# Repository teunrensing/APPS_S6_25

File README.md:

# APPS_S6_25
Dit is een repo voor het APPS project

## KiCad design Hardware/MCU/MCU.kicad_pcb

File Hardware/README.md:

# APPS_S6_25 Hardware
APPS Hardware

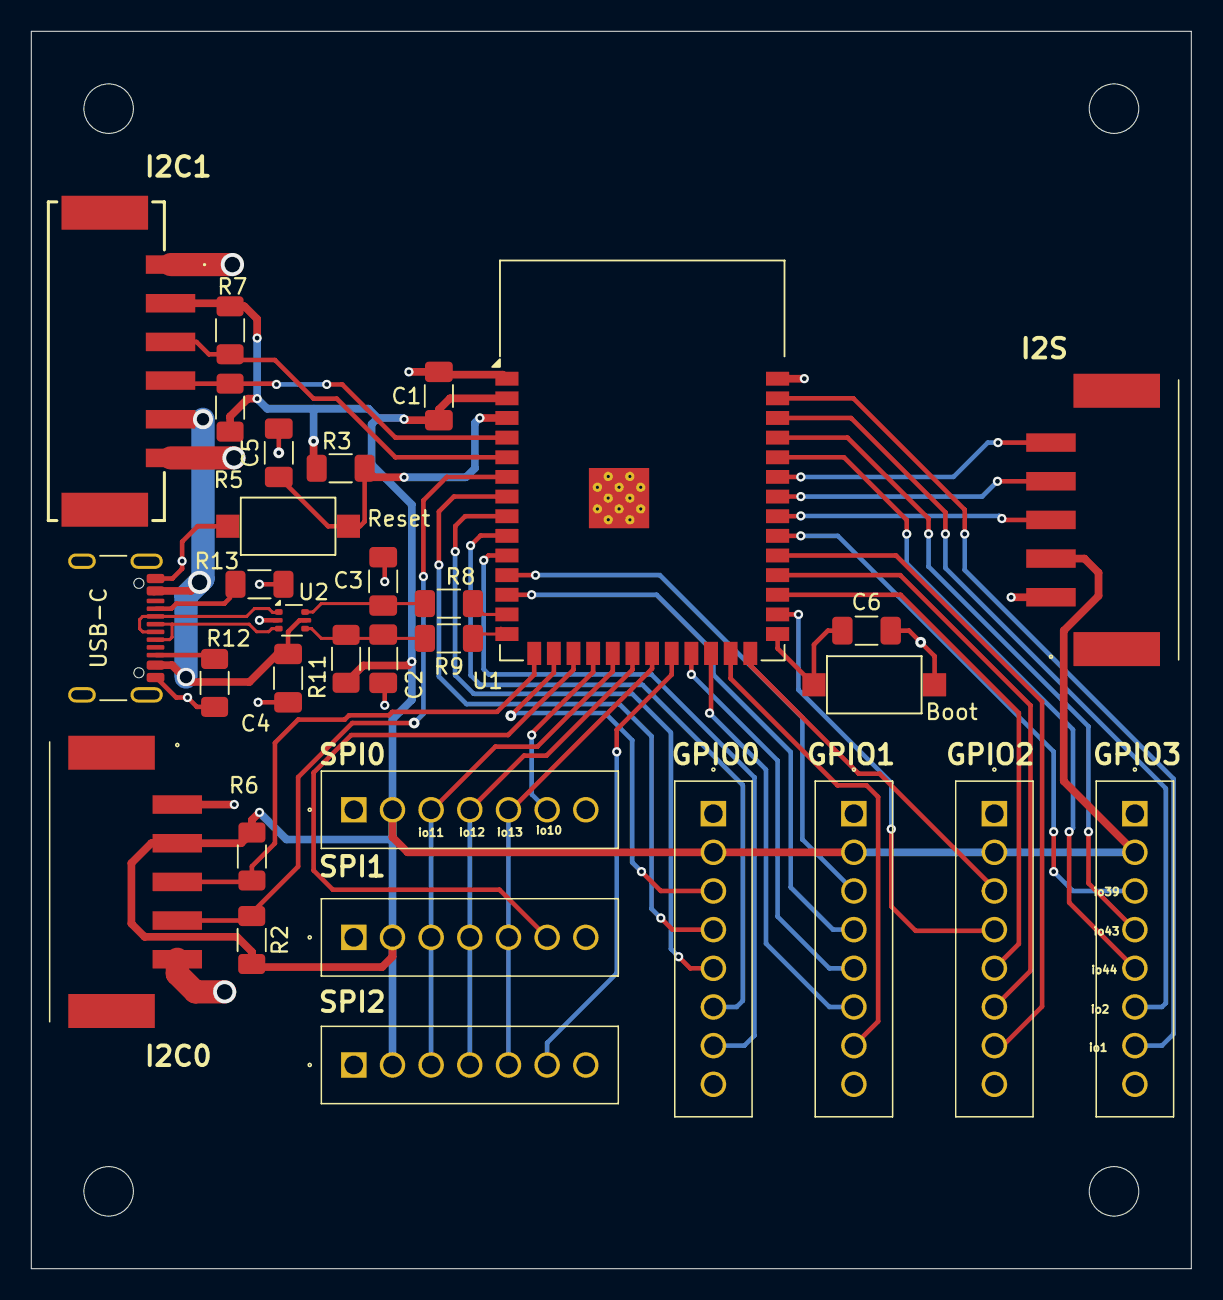
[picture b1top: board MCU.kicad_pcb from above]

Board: 4 copper layers, 75.0 x 80.0 mm, 35 parts (0 on the bottom side), 47 nets.

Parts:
Boot: SW_Push; SW_SPST_CK_RS282G05A3
C1: 100n; C_1206_3216Metric_Pad1.33x1.80mm_HandSolder
C2, C3: C; C_1206_3216Metric_Pad1.33x1.80mm_HandSolder
C4: 100nf; C_1206_3216Metric_Pad1.33x1.80mm_HandSolder
C5, C6: 1u; C_1206_3216Metric_Pad1.33x1.80mm_HandSolder
GPIO0, GPIO1, GPIO2, GPIO3: 1778612
H1, H2, H3, H4: MountingHole; MountingHole_3.2mm_M3
I2C0: i2c1; 1814948
I2C1: i2c0; 1814951
I2S: i2s; 1814948
R2, R5, R6, R7: 4k7; R_1206_3216Metric_Pad1.30x1.75mm_HandSolder
R3: 10k; R_1206_3216Metric_Pad1.30x1.75mm_HandSolder
R8, R9: 0; R_1206_3216Metric_Pad1.30x1.75mm_HandSolder
R11, R12, R13: 5k1; R_1206_3216Metric_Pad1.30x1.75mm_HandSolder
Reset: SW_Push; SW_SPST_CK_RS282G05A3
SPI0: spi0; 1778609
SPI1: sp1; 1778609
SPI2: sp2; 1778609
U1: ESP32-S3-WROOM-1
U2: USBLC6-2P6; SOT-666
USB-C: USB_C_Receptacle_USB2.0_16P; USB_C_Receptacle_GCT_USB4105-xx-A_16P_TopMnt_Horizontal

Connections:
+: C2.2, R9.2, R11.2, U2.4 (I/O2)
+3.3V: C1.2, GPIO0.2, GPIO1.2, GPIO2.2, GPIO3.2, I2C0.2, I2C1.2, I2S.2, R2.2, R3.1, R5.2, R6.1, R7.1, R11.1, SPI0.2, SPI1.2, SPI2.2, U1.2 (3V3)
+5Vin: GPIO0.8, GPIO1.8, GPIO2.8, GPIO3.8, I2C0.5, I2C1.6, SPI0.7, SPI1.7, SPI2.7
+5Vout: C4.1, I2C1.5, U2.5 (VBUS), USB-C.A4 (VBUS), USB-C.A9 (VBUS), USB-C.B4 (VBUS), USB-C.B9 (VBUS)
-: C3.2, R8.2, U2.6 (I/O1)
GND: Boot.2, C1.1, C2.1, C3.1, C4.2, C5.2, C6.2, GPIO0.1, GPIO1.1, GPIO2.1, GPIO3.1, I2C0.1, I2C1.1, I2S.1, R12.1, R13.1, Reset.2, SPI0.1, SPI1.1, SPI2.1, U1.1 (GND), U1.40 (GND), U1.41 (GND), U2.2 (GND), USB-C.A1 (GND), USB-C.A12 (GND), USB-C.B1 (GND), USB-C.B12 (GND), USB-C.S1 (SHIELD)
unnamed: R13.2, USB-C.A5 (CC1)
unnamed: R12.2, USB-C.B5 (CC2)
unnamed: U2.3 (I/O2), USB-C.A6 (D+), USB-C.B6 (D+)
unnamed: U2.1 (I/O1), USB-C.A7 (D-), USB-C.B7 (D-)
unnamed: R9.1, U1.14 (USB_D+)
unnamed: R8.1, U1.13 (USB_D-)
boot0: Boot.1, C6.1, U1.27 (IO0)
i2s sck: I2S.3, U1.33 (IO40)
i2s sd: I2S.5, U1.35 (IO42)
i2s ws: I2S.4, U1.34 (IO41)
io1: GPIO3.7, U1.39 (IO1)
io2: GPIO3.6, U1.38 (IO2)
io7: GPIO0.4, U1.7 (IO7)
io8: GPIO1.4, U1.12 (IO8)
io15: GPIO0.5, U1.8 (IO15)
io16: GPIO0.6, U1.9 (IO16)
io17: GPIO0.7, U1.10 (IO17)
io18: GPIO1.3, U1.11 (IO18)
io21: GPIO1.5, U1.23 (IO21)
io35: GPIO2.4, U1.28 (IO35)
io36: GPIO2.5, U1.29 (IO36)
io37: GPIO2.6, U1.30 (IO37)
io38: GPIO2.7, U1.31 (IO38)
io39: GPIO3.3, U1.32 (IO39)
io45: GPIO2.3, U1.26 (IO45)
io46: GPIO0.3, U1.16 (IO46)
io47: GPIO1.6, U1.24 (IO47)
io48: GPIO1.7, U1.25 (IO48)
miso: SPI0.5, SPI1.5, SPI2.5, U1.21 (IO13)
mosi: SPI0.3, SPI1.3, SPI2.3, U1.19 (IO11)
reset: C5.1, R3.2, Reset.1, U1.3 (EN)
rxd0: GPIO3.5, U1.36 (RXD0)
sck: SPI0.4, SPI1.4, SPI2.4, U1.20 (IO12)
scl0: I2C0.4, R2.1, U1.6 (IO6)
scl1: I2C1.4, R5.1, U1.4 (IO4)
sda0: I2C0.3, R6.2, U1.15 (IO3)
sda1: I2C1.3, R7.2, U1.5 (IO5)
ss0: SPI0.6, U1.18 (IO10)
ss1: SPI1.6, U1.17 (IO9)
ss2: SPI2.6, U1.22 (IO14)
txd0: GPIO3.4, U1.37 (TXD0)

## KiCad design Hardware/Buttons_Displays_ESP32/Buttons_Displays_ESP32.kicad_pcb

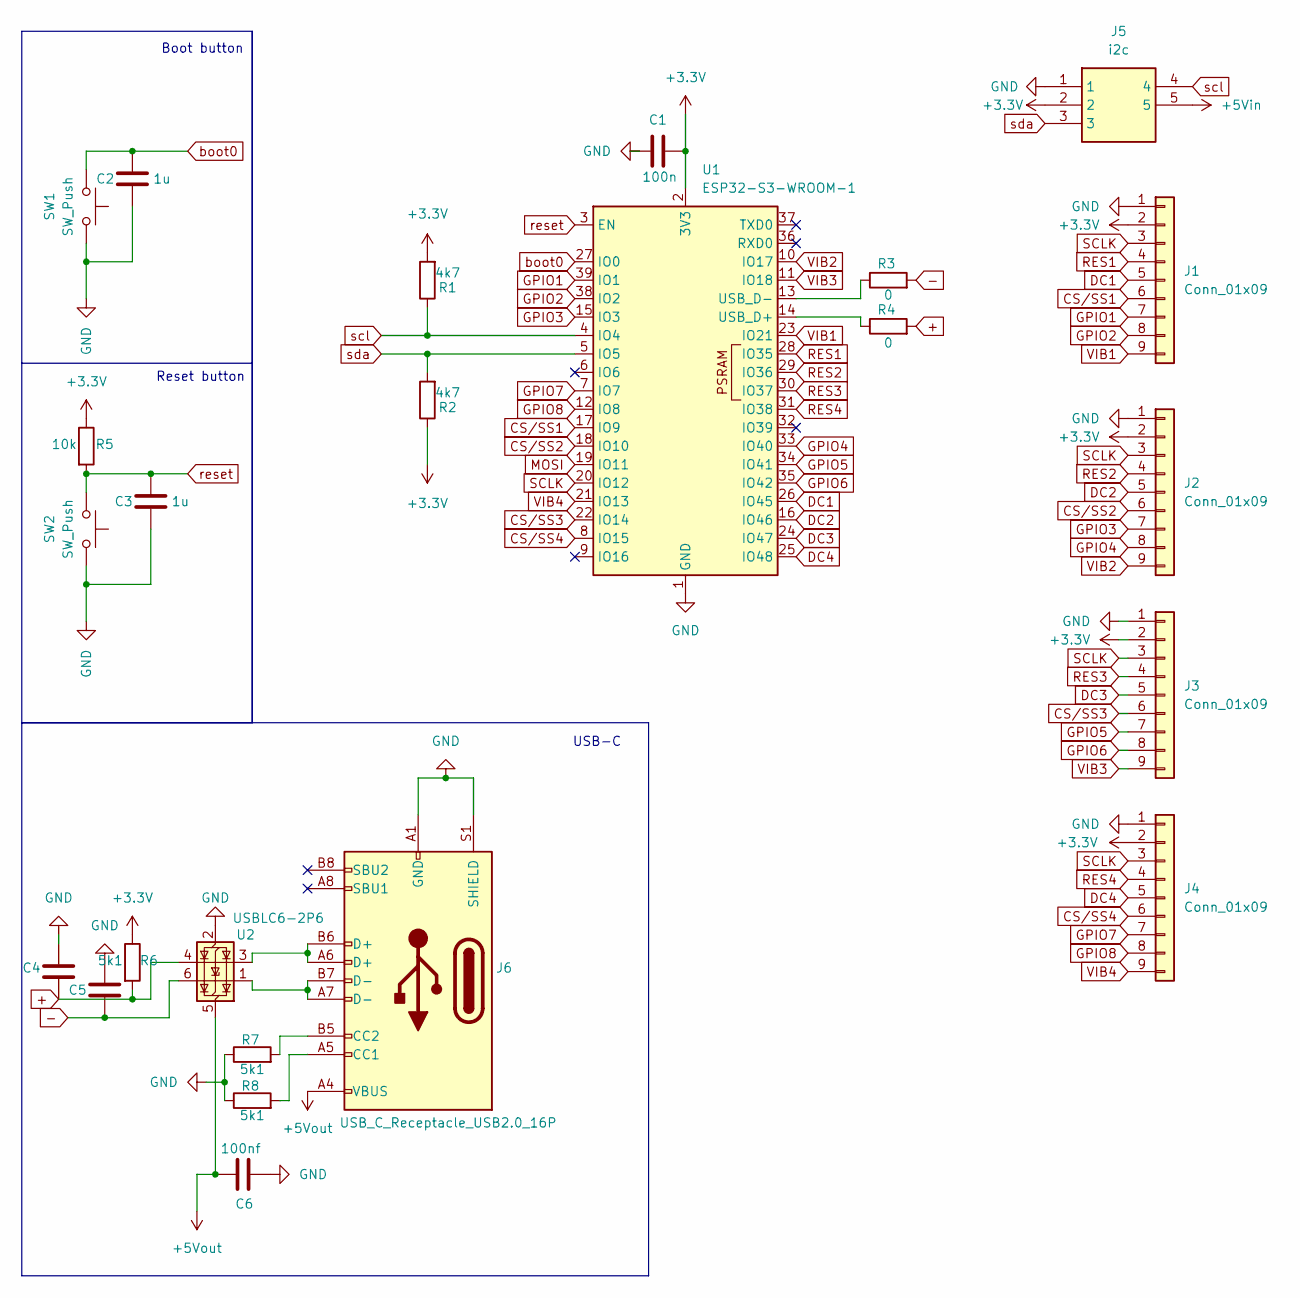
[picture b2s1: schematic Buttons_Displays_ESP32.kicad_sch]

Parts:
C1: 100n; C_1206_3216Metric_Pad1.33x1.80mm_HandSolder
C2, C3: 1u; C_1206_3216Metric_Pad1.33x1.80mm_HandSolder
C4, C5: C; C_1206_3216Metric_Pad1.33x1.80mm_HandSolder
C6: 100nf; C_1206_3216Metric_Pad1.33x1.80mm_HandSolder
J1, J2, J3, J4: Conn_01x09; JST_XH_B9B-XH-A_1x09_P2.50mm_Vertical
J5: i2c; 1814948; Mouser Part Number 651-1814948
J6: USB_C_Receptacle_USB2.0_16P; USB_C_Receptacle_GCT_USB4105-xx-A_16P_TopMnt_Horizontal
R1, R2: 4k7; R_1206_3216Metric_Pad1.30x1.75mm_HandSolder
R3, R4: 0; R_1206_3216Metric_Pad1.30x1.75mm_HandSolder
R5: 10k; R_1206_3216Metric_Pad1.30x1.75mm_HandSolder
R6, R7, R8: 5k1; R_1206_3216Metric_Pad1.30x1.75mm_HandSolder
SW1, SW2: SW_Push; SW_SPST_CK_RS282G05A3
U1: ESP32-S3-WROOM-1
U2: USBLC6-2P6; SOT-666

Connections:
+: C4.2, R4.2, R6.2, U2.4 (I/O2)
+3.3V: C1.2, J1.2, J2.2, J3.2, J4.2, J5.2, R1.2, R2.1, R5.1, R6.1, U1.2 (3V3)
+5Vin: J5.5
+5Vout: C6.1, J6.A4 (VBUS), J6.A9 (VBUS), J6.B4 (VBUS), J6.B9 (VBUS), U2.5 (VBUS)
-: C5.2, R3.2, U2.6 (I/O1)
CS/SS1: J1.6, U1.17 (IO9)
CS/SS2: J2.6, U1.18 (IO10)
CS/SS3: J3.6, U1.22 (IO14)
CS/SS4: J4.6, U1.8 (IO15)
DC1: J1.5, U1.26 (IO45)
DC2: J2.5, U1.16 (IO46)
DC3: J3.5, U1.24 (IO47)
DC4: J4.5, U1.25 (IO48)
GND: C1.1, C2.2, C3.2, C4.1, C5.1, C6.2, J1.1, J2.1, J3.1, J4.1, J5.1, J6.A1 (GND), J6.A12 (GND), J6.B1 (GND), J6.B12 (GND), J6.S1 (SHIELD), R7.1, R8.1, SW1.2, SW2.2, U1.1 (GND), U1.40 (GND), U1.41 (GND), U2.2 (GND)
GPIO1: J1.7, U1.39 (IO1)
GPIO2: J1.8, U1.38 (IO2)
GPIO3: J2.7, U1.15 (IO3)
GPIO4: J2.8, U1.33 (IO40)
GPIO5: J3.7, U1.34 (IO41)
GPIO6: J3.8, U1.35 (IO42)
GPIO7: J4.7, U1.7 (IO7)
GPIO8: J4.8, U1.12 (IO8)
MOSI: U1.19 (IO11)
unnamed: J6.A5 (CC1), R8.2
unnamed: J6.B5 (CC2), R7.2
unnamed: J6.A6 (D+), J6.B6 (D+), U2.3 (I/O2)
unnamed: J6.A7 (D-), J6.B7 (D-), U2.1 (I/O1)
unnamed: R4.1, U1.14 (USB_D+)
unnamed: R3.1, U1.13 (USB_D-)
RES1: J1.4, U1.28 (IO35)
RES2: J2.4, U1.29 (IO36)
RES3: J3.4, U1.30 (IO37)
RES4: J4.4, U1.31 (IO38)
SCLK: J1.3, J2.3, J3.3, J4.3, U1.20 (IO12)
VIB1: J1.9, U1.23 (IO21)
VIB2: J2.9, U1.10 (IO17)
VIB3: J3.9, U1.11 (IO18)
VIB4: J4.9, U1.21 (IO13)
boot0: C2.1, SW1.1, U1.27 (IO0)
reset: C3.1, R5.2, SW2.1, U1.3 (EN)
scl: J5.4, R1.1, U1.4 (IO4)
sda: J5.3, R2.2, U1.5 (IO5)

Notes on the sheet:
Boot button
USB-C
Reset button

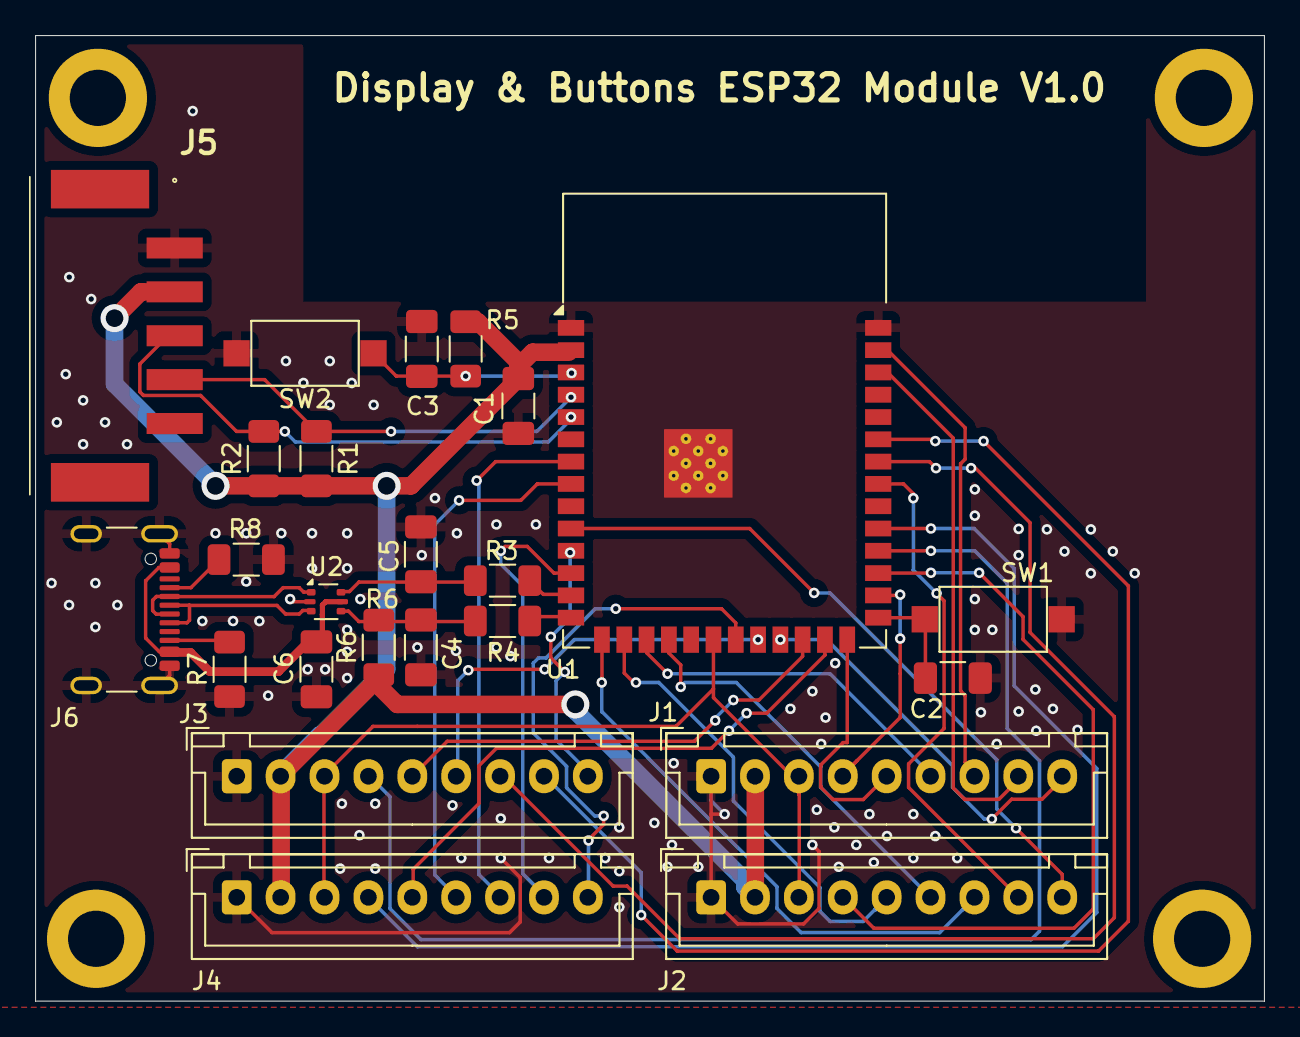
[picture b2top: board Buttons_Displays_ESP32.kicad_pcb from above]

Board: 2 copper layers, 70.0 x 55.0 mm, 24 parts (0 on the bottom side), 40 nets.

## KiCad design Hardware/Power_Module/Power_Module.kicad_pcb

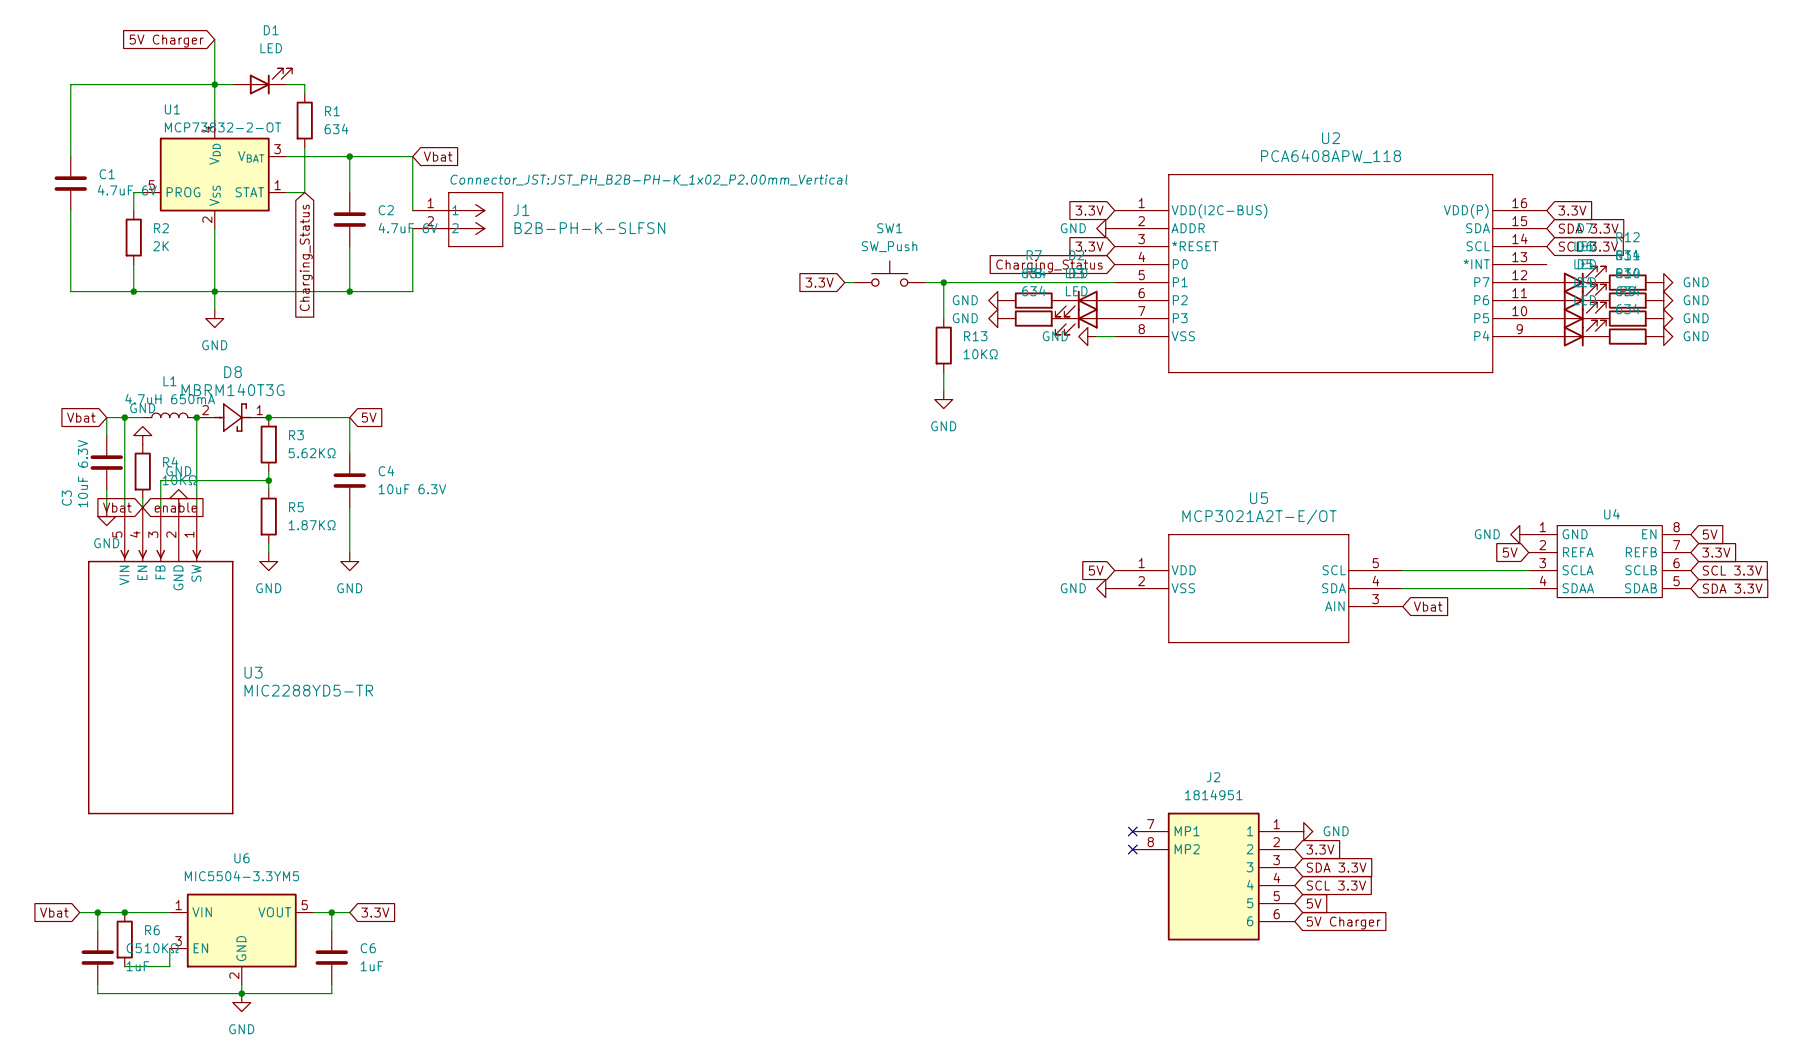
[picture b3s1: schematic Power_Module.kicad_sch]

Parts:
C1, C2: 4.7uF 6V; C_1206_3216Metric
C3, C4: 10uF 6.3V; C_0805_2012Metric
C5, C6: 1uF; C_0402_1005Metric
D1, D2, D3, D4, D5, D6, D7: LED; LED_0402_1005Metric
D8: MBRM140T3G; D_SOD-123
J1: B2B-PH-K-SLFSN; JST_PH_B2B-PH-K_1x02_P2.00mm_Vertical
J2: 1814951; Manufacturer_Part_Number 1814951; Mouser Part Number 651-1814951
L1: 4.7uH 650mA; C_1210_3225Metric
R1, R7, R8, R9, R10, R11, R12: 634; C_0402_1005Metric
R2: 2K; R_0402_1005Metric
R3: 5.62KΩ; R_0603_1608Metric
R4, R6, R13: 10KΩ; R_0603_1608Metric
R5: 1.87KΩ; R_0603_1608Metric
SW1: SW_Push; SW_Tactile_SPST_NO_Straight_CK_PTS636Sx25SMTRLFS
U1: MCP73832-2-OT; SOT-23-5
U2: PCA6408APW_118; TSSOP-16_4.4x5mm_P0.65mm
U3: MIC2288YD5-TR; TSOT-23-5
U4: TSSOP-8_3x3mm_P0.65mm
U5: MCP3021A2T-E/OT; TSOT-23-5
U6: MIC5504-3.3YM5; SOT-23-5

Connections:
3.3V: C6.1, J2.2, SW1.1, U2.1 (VDD(I2C-BUS)), U2.3 (*RESET), U2.16 (VDD(P)), U4.7 (REFB), U6.5 (VOUT)
5V: C4.1, D8.1, J2.5, R3.2, U4.2 (REFA), U4.8 (EN), U5.1 (VDD)
5V Charger: C1.1, D1.2 (A), J2.6, U1.4 (V_{DD})
Charging_Status: R1.2, U1.1 (STAT), U2.4 (P0)
GND: C1.2, C2.2, C3.2, C4.2, C5.2, C6.2, J1.2, J2.1, R2.2, R4.1, R5.2, R7.1, R8.1, R9.2, R10.2, R11.2, R12.2, R13.2, U1.2 (V_{SS}), U2.2 (ADDR), U2.8 (VSS), U3.2 (GND), U4.1 (GND), U5.2 (VSS), U6.2 (GND)
unnamed: D1.1 (K), R1.1
unnamed: D2.2 (A), U2.6 (P2)
unnamed: D2.1 (K), R7.2
unnamed: D3.2 (A), U2.7 (P3)
unnamed: D3.1 (K), R8.2
unnamed: D4.2 (A), U2.9 (P4)
unnamed: D4.1 (K), R9.1
unnamed: D5.2 (A), U2.10 (P5)
unnamed: D5.1 (K), R10.1
unnamed: D6.2 (A), U2.11 (P6)
unnamed: D6.1 (K), R11.1
unnamed: D7.2 (A), U2.12 (P7)
unnamed: D7.1 (K), R12.1
unnamed: R2.1, U1.5 (PROG)
unnamed: R13.1, SW1.2, U2.5 (P1)
unnamed: R3.1, R5.1, U3.3 (FB)
unnamed: D8.2, L1.2, U3.1 (SW)
unnamed: U4.3 (SCLA), U5.5 (SCL)
unnamed: U4.4 (SDAA), U5.4 (SDA)
unnamed: R6.2, U6.3 (EN)
SCL 3.3V: J2.4, U2.14 (SCL), U4.6 (SCLB)
SDA 3.3V: J2.3, U2.15 (SDA), U4.5 (SDAB)
Vbat: C2.1, C3.1, C5.1, J1.1, L1.1, R4.2, R6.1, U1.3 (V_{BAT}), U3.4 (EN), U3.5 (VIN), U5.3 (AIN), U6.1 (VIN)

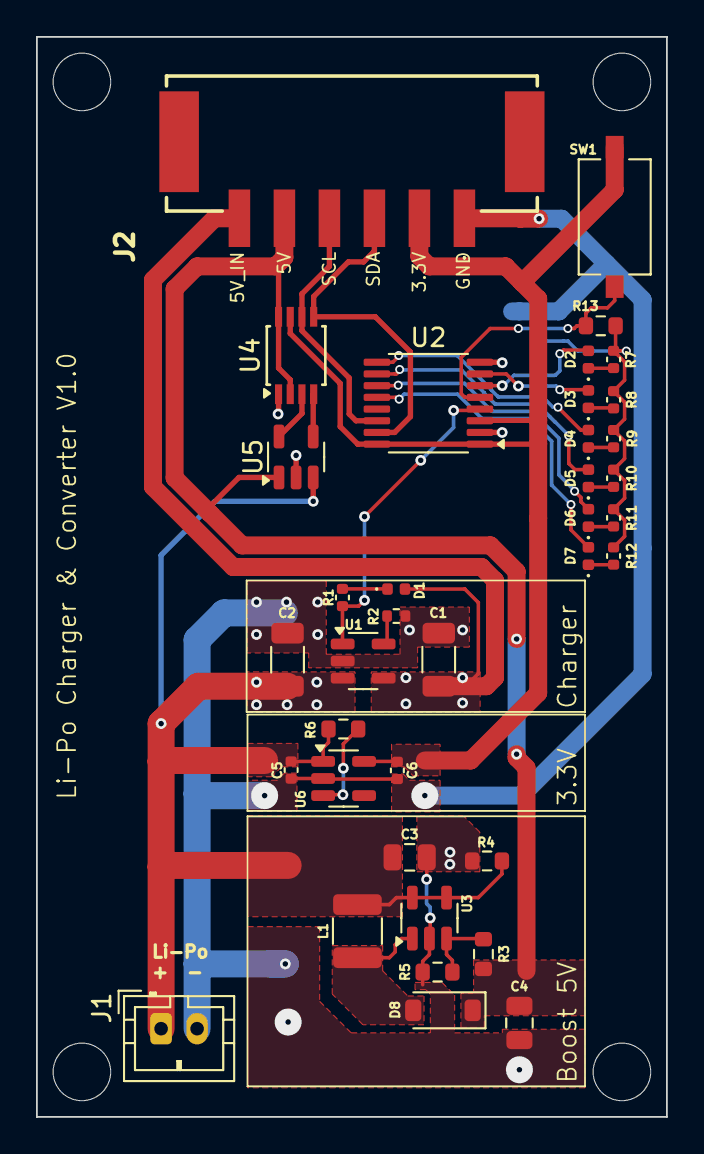
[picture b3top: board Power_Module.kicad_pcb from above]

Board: 2 copper layers, 35.0 x 60.0 mm, 37 parts (0 on the bottom side), 28 nets.

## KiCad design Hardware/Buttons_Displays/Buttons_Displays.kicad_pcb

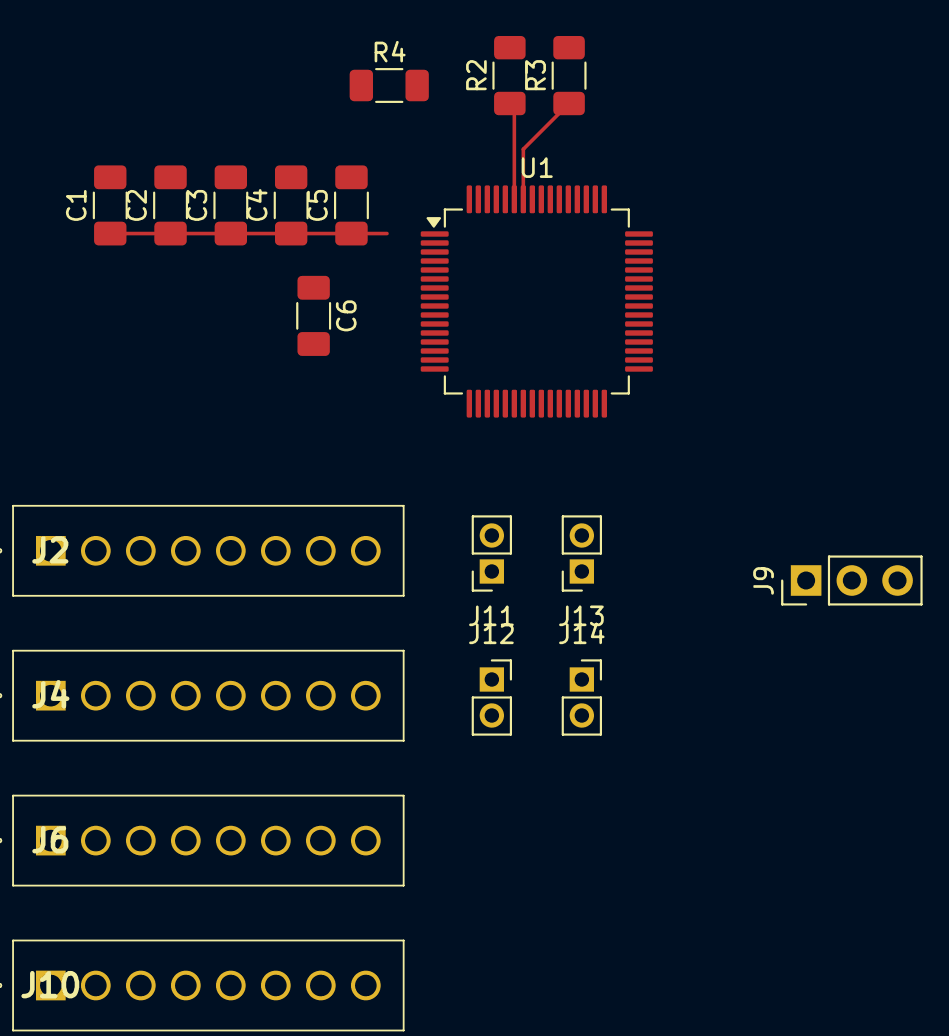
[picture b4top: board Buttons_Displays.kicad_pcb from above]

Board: 2 copper layers, 19 parts (0 on the bottom side), 26 nets.

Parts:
C1: 10u; C_1206_3216Metric_Pad1.33x1.80mm_HandSolder
C2, C3, C4, C5, C6: 100n; C_1206_3216Metric_Pad1.33x1.80mm_HandSolder
J2, J4, J6, J10: Conn_01x08; 1778612
J9: Conn_01x03; PinHeader_1x03_P2.54mm_Vertical
J11, J12, J13, J14: Conn_01x02; PinSocket_1x02_P2.00mm_Vertical
R2, R3: 4k7; R_1206_3216Metric_Pad1.30x1.75mm_HandSolder
R4: 10k; R_1206_3216Metric_Pad1.30x1.75mm_HandSolder
U1: STM32H523RETx; LQFP-64_10x10mm_P0.5mm

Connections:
+3.3V: C1.1, C2.1, C3.1, C4.1, C5.1, J2.7, J4.7, J6.7, J10.7, R2.2, R3.2, U1.1 (VBAT), U1.19 (VDD), U1.32 (VDD), U1.48 (VDD), U1.64 (VDD)
CS/SS: J2.2, J4.2, J6.2, J10.2, U1.20 (PA4)
DC1: J10.3, U1.8 (PC0)
DC2: J2.3, U1.9 (PC1)
DC3: J4.3, U1.10 (PC2)
DC4: J6.3, U1.11 (PC3)
GND: C1.2, C2.2, C3.2, C4.2, C5.2, C6.2, J2.1, J4.1, J6.1, J10.1, J11.1, J12.1, J13.1, J14.1, U1.12 (VSSA), U1.18 (VSS), U1.31 (VSS), U1.47 (VSS), U1.63 (VSS)
GPIO1: J10.8, U1.26 (PB0)
GPIO2: J11.2, U1.27 (PB1)
GPIO3: J2.8, U1.28 (PB2)
GPIO4: J12.2, U1.57 (PB5)
GPIO5: J4.8, U1.61 (PB8)
GPIO6: J13.2, U1.29 (PB10)
GPIO7: J6.8, U1.33 (PB12)
GPIO8: J14.2, U1.34 (PB13)
NRST: C6.1, J9.3, U1.7 (NRST)
unnamed: R4.2, U1.60 (BOOT0)
RES1: J10.4, U1.41 (PA8)
RES2: J2.4, U1.42 (PA9)
RES3: J4.4, U1.43 (PA10)
RES4: J6.4, U1.44 (PA11)
SCLK: J2.6, J4.6, J6.6, J10.6, U1.21 (PA5)
SWCLK: J9.1, U1.49 (PA14(JTCK)
SWDIO: J9.2, U1.46 (PA13(JTMS)
scl: R2.1, U1.59 (PB7)
sda: R3.1, U1.58 (PB6)

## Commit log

2025-02-06 Folders toegevoegd
2025-02-06 Ignore naar de software folder
2025-02-06 kicad gitignore
2025-02-13 kicad project
2025-02-19 inmp + mp3player
2025-02-19 added MCU
2025-03-12 Added power module project
2025-03-12 buttondisplay
2025-03-12 added gnd for test
2025-03-13 MCU schema bijgewerkt
2025-03-19 aantal pinnen
2025-03-19 vergeten update
2025-03-21 added powermodule ic
2025-03-21 Initial commit for Demo
2025-03-27 mcu design updated met layout en traces
2025-03-27 updated traces en layout
2025-03-27 mierenneukerij
2025-04-02 schematische tekening geordend
2025-04-02 added usb weerstanden
2025-04-02 edited footprint buttons
2025-04-03 silkscreen aangepast
2025-04-03 boot en reset pin configuratie veranderd, pull up veranderd en capcitoren toegevoegd
2025-04-03 new footprint usb-c
2025-04-03 silckscreen!
2025-04-03 gerber
2025-04-03 0.10
2025-04-03 add zip
2025-04-09 footprints
2025-04-24 pcb scherm met esp32
2025-05-07 pcb schermpjes af
2025-05-07 text aangepast
2025-05-07 kleine aanpassingen
2025-05-07 mounting holes
2025-05-08 pcb outlines
2025-05-14 reset pin wel aangesloten
2025-05-15 Kut ipo ;)
    IO pin voor tril motor toegevoegd
2025-05-15 laatste aanpassingen
2025-05-15 model
2025-05-15 hoogte aangepast
    hoogte pcb is nu 55mm
2025-05-16 Added power module pcb
2025-05-16 Added LED Matrix for fun
2025-05-21 geber files
2025-05-21 small silkscreen changes
2025-06-13 Added code
2025-06-18 updated code
2025-06-26 added new code
2025-06-26 added new files for bitmaps
2025-06-28 Used SPI hardware for displays
2025-07-01 Added EEZ project
2025-07-05 Added: lv_tick_inc calls
    Necessary to display and update screens.
2026-01-17 Goodbye git
2026-01-17 Hello git
2026-01-20 Added documentation
